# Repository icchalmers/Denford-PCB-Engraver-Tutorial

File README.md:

# Denford PCB Engraver Tutorial

This tutorial will lead you through using the [Denford PCB Engraver](https://denford.co.uk/products/pcb-engraver/) to mill a small breakout board for a surface mount ATtiny85. The tutorial was written specifically for the FabLab at the University of Strathclyde, but should be applicable to anyone with a Denford PCB Engraver.

The best way to use the tutorial is in the browser. You can start at the beginning my going to the [Introduction](doc/introduction.md) or use the [Index](doc/index.md) to jump straight to a specific section.

The [latest release](https://github.com/icchalmers/Denford-PCB-Engraver-Tutorial/releases/latest) of the tutorial includes all of the example files and also has a PDF version that is easier for printing.

# Author

This tutorial was written by [Iain Chalmers](https://www.linkedin.com/in/iain-chalmers-0394753b). Any feedback is greatly appreciated and can be submitted by [opening an issue](https://github.com/icchalmers/Denford-PCB-Engraver-Tutorial/issues/new) on GitHub.

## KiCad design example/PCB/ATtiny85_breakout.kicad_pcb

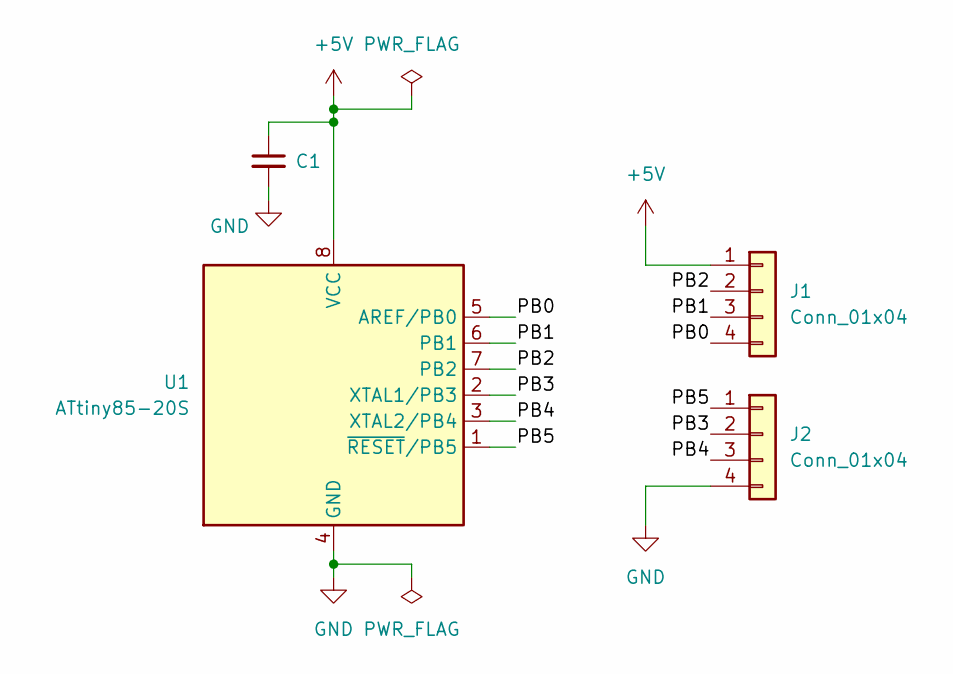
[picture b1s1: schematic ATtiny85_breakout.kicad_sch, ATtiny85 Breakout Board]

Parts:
C1: C_Small; C_1206_3216Metric_Pad1.33x1.80mm_HandSolder
J1, J2: Conn_01x04; PinHeader_1x04_P2.54mm_Vertical
U1: ATtiny85-20S; SOIC-8W_5.3x5.3mm_P1.27mm

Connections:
+5V: C1.1, J1.1, U1.8 (VCC)
/PB0: J1.4, U1.5 (AREF/PB0)
/PB1: J1.3, U1.6 (PB1)
/PB2: J1.2, U1.7 (PB2)
/PB3: J2.2, U1.2 (XTAL1/PB3)
/PB4: J2.3, U1.3 (XTAL2/PB4)
/PB5: J2.1, U1.1 (~RESET/PB5)
GND: C1.2, J2.4, U1.4 (GND)

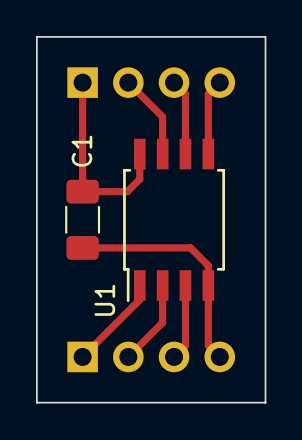
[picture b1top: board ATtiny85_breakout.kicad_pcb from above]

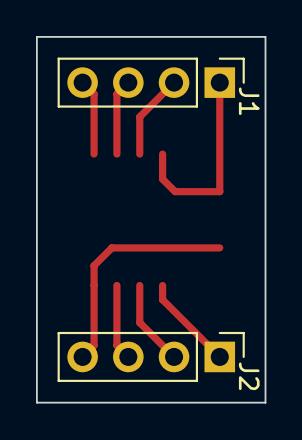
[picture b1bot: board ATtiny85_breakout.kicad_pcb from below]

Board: 2 copper layers, 12.7 x 20.3 mm, 4 parts (2 on the bottom side), 8 nets.

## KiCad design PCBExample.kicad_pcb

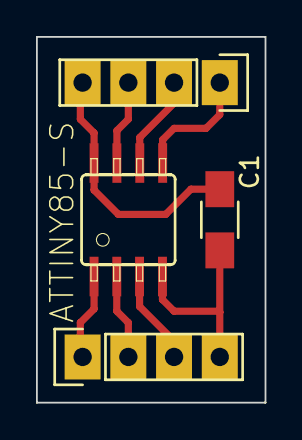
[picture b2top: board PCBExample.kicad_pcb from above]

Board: 2 copper layers, 12.7 x 20.3 mm, 4 parts (0 on the bottom side), 8 nets.

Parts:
C1: 0.1u; C_1206_HandSoldering_IainEdit
IC1: ATTINY85-S; avr-SOIC8
P1, P2: CONN_01X04; Socket_Strip_Straight_1x04

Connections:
+5V: C1.1, IC1.8, P1.4
GND: C1.2, IC1.4, P2.4
unnamed: IC1.1, P2.1
unnamed: IC1.2, P2.2
unnamed: IC1.3, P2.3
unnamed: IC1.5, P1.1
unnamed: IC1.6, P1.2
unnamed: IC1.7, P1.3

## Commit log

2015-08-29 First commit of KiCAD project files
2015-08-29 Adding licence
2015-08-29 Adding gerbers
2015-08-30 Adding original and fixed drill files, generated trace mill .fnc and generated and original cutting fnc
2015-10-26 Adding first draft of the tutorial write up
2018-07-02 Change to CC BY-SA 4.0 licence
2018-07-02 Update based on user feedback
2018-07-02 Update PDF with changes
2018-08-14 Update tomake it clearer that setting the Z height should be done with a drill bit set at 2 mm depth
2023-03-27 Remove old tutorial example files
    I'll update to KiCAD 6.0 and just use default included footprints.
2023-03-27 Add KiCAD 6.0 example PCB
    This is just a remake of the original example PCB, but uses only footprints found in the default KiCAD 6.0 install.
2023-03-27 Add example gerber output
2023-03-27 Add pcb2gcode settings file for Denford
2023-03-27 Add example pcb2gcode output
2023-04-04 Fix caps on folder name
2023-04-04 Ignore vscode history folder
2023-04-04 Initial introduction
    Plus some placeholders files to allow linking.
2023-04-04 Fix relative links
2023-04-04 Add software used overview
2023-04-05 Add link to KiCAD getting started tutorial
    Also switched to relative doc links.
    A few minor corrections.
2023-04-05 Add outro to engraver overview
2023-04-05 Add link back to index
2023-04-05 Add note on inductions and feedback
2023-04-05 Add missing link
2023-04-05 Add machine overview
2023-04-05 Added machine capabilities/limitations
2023-04-05 Add use case recommendations
2023-04-05 Gerber generation intro
2023-04-05 Fix links
2023-04-05 Add stub files for missing sections
2023-06-06 Add no silkscreen note
2023-06-06 Fix link to be to latest
2023-06-06 Minor typo fixes
2023-06-06 Add DRC constraints section
2023-06-06 Add KiCAD gerber export settings section
2023-06-06 Inital pcb2gcode section
2023-06-06 Typo fix
2023-06-06 Fix section order
2023-06-06 Add note about default bit assumptions
